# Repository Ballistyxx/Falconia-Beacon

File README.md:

# Falconia Beacon

Falconia Beacon is an ATTINY816-based, CR2032-powered LED beacon board used to make the Falconia rover visible to the SMCS Pi-in-the-sky satellite.

## What It Does

- Blinks onboard LEDs so the satellite can detect the rover location.
- Uses a potentiometer to enable or disable the blinking program.
- Supports I2C control at address `0x42`.

## Project Layout

- `PCB/`  
  Hardware design and manufacturing assets:
  - KiCad schematic and PCB files
  - 3D models and custom footprints/symbol libraries
  - Panelization and production outputs

- `src/`  
  Firmware source flashed to the board by default:
  - Main beacon firmware and related examples
  - Build files (Makefile)

## Hardware Summary

- MCU: Microchip ATTINY816
- Power: CR2032 coin cell
- Interface: I2C (address `0x42`)
- User control: Potentiometer (blink program on/off)

## Firmware

The default board firmware lives in `src/` and is intended to be the code programmed onto production boards unless otherwise noted.

Typical workflow:

1. Build firmware from the `src/` directory.
2. Flash using your ATTINY816 programming setup.
3. Validate LED blink behavior and I2C response at address `0x42`.

## Notes

- Hardware and firmware are versioned together in this repository.
- For board-level updates, start in `PCB/`.
- For behavior/protocol updates, start in `src/`.

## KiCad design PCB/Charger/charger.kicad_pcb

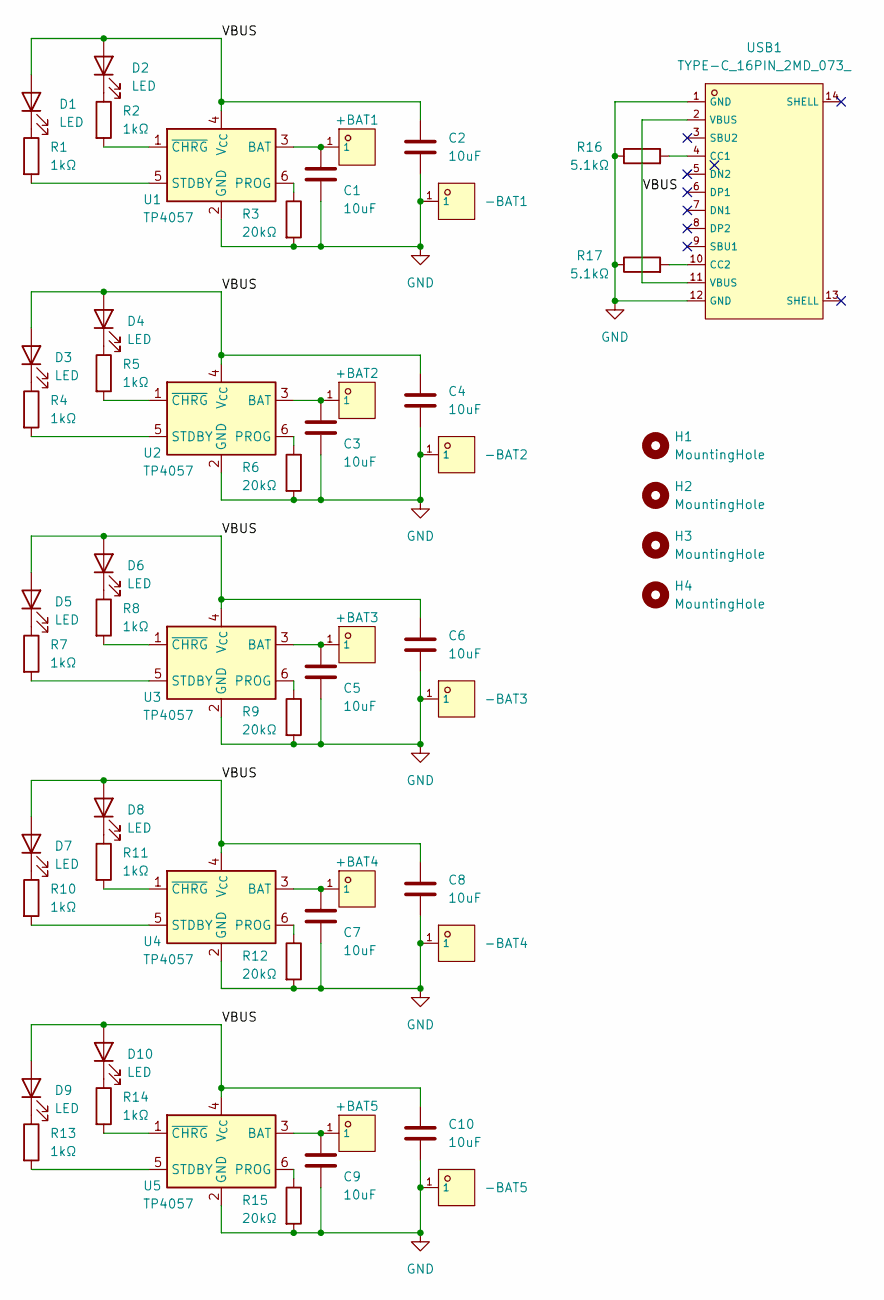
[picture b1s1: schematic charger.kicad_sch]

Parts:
+BAT1, +BAT2, +BAT3, +BAT4, +BAT5: YTC1P-6030-01; SMD-1_BD2.0-H10.0; LCSC C5221285
-BAT1, -BAT2, -BAT3, -BAT4, -BAT5: YTC1P-6030-01; SMD-1_BD2.0-H10.0; LCSC C5221285
C1, C2, C3, C4, C5, C6, C7, C8, C9, C10: 10uF; C_0603_1608Metric
D1, D2, D3, D4, D5, D6, D7, D8, D9, D10: LED; LED_0603_1608Metric
H1, H2, H3, H4: MountingHole; MountingHole_3.2mm_M3_ISO7380_Pad
R1, R2, R4, R5, R7, R8, R10, R11, R13, R14: 1kΩ; R_0603_1608Metric
R3, R6, R9, R12, R15: 20kΩ; R_0603_1608Metric
R16, R17: 5.1kΩ; R_0805_2012Metric
U1, U2, U3, U4, U5: TP4057; TSOT-23-6
USB1: TYPE-C_16PIN_2MD_073_; USB-C-SMD_TYPE-C-6PIN-2MD-073; LCSC C2765186

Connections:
/VBUS: C2.1, C4.1, C6.1, C8.1, C10.1, D1.2 (A), D2.2 (A), D3.2 (A), D4.2 (A), D5.2 (A), D6.2 (A), D7.2 (A), D8.2 (A), D9.2 (A), D10.2 (A), U1.4 (V_{CC}), U2.4 (V_{CC}), U3.4 (V_{CC}), U4.4 (V_{CC}), U5.4 (V_{CC}), USB1.2 (VBUS), USB1.11 (VBUS)
GND: -BAT1.1, -BAT2.1, -BAT3.1, -BAT4.1, -BAT5.1, C1.2, C2.2, C3.2, C4.2, C5.2, C6.2, C7.2, C8.2, C9.2, C10.2, R3.2, R6.2, R9.2, R12.2, R15.2, R16.1, R17.1, U1.2 (GND), U2.2 (GND), U3.2 (GND), U4.2 (GND), U5.2 (GND), USB1.1 (GND), USB1.12 (GND)
unnamed: D1.1 (K), R1.1
unnamed: D2.1 (K), R2.1
unnamed: D3.1 (K), R4.1
unnamed: D4.1 (K), R5.1
unnamed: D5.1 (K), R7.1
unnamed: D6.1 (K), R8.1
unnamed: D7.1 (K), R10.1
unnamed: D8.1 (K), R11.1
unnamed: D9.1 (K), R13.1
unnamed: D10.1 (K), R14.1
unnamed: +BAT1.1, C1.1, U1.3 (BAT)
unnamed: R3.1, U1.6 (PROG)
unnamed: R1.2, U1.5 (STDBY)
unnamed: R2.2, U1.1 (~CHRG)
unnamed: +BAT2.1, C3.1, U2.3 (BAT)
unnamed: R6.1, U2.6 (PROG)
unnamed: R4.2, U2.5 (STDBY)
unnamed: R5.2, U2.1 (~CHRG)
unnamed: +BAT3.1, C5.1, U3.3 (BAT)
unnamed: R9.1, U3.6 (PROG)
unnamed: R7.2, U3.5 (STDBY)
unnamed: R8.2, U3.1 (~CHRG)
unnamed: +BAT4.1, C7.1, U4.3 (BAT)
unnamed: R12.1, U4.6 (PROG)
unnamed: R10.2, U4.5 (STDBY)
unnamed: R11.2, U4.1 (~CHRG)
unnamed: +BAT5.1, C9.1, U5.3 (BAT)
unnamed: R15.1, U5.6 (PROG)
unnamed: R13.2, U5.5 (STDBY)
unnamed: R14.2, U5.1 (~CHRG)
unnamed: R16.2, USB1.4 (CC1)
unnamed: R17.2, USB1.10 (CC2)

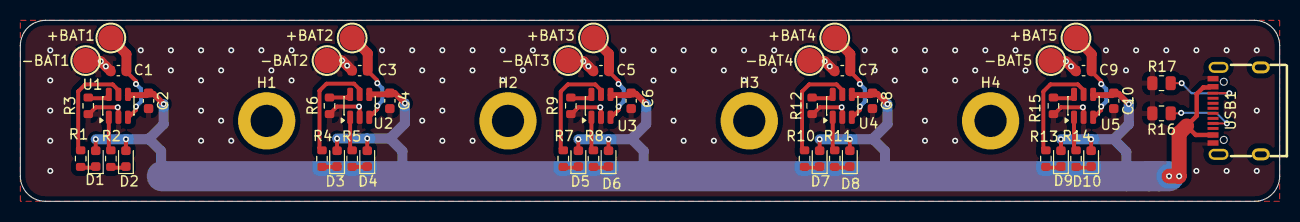
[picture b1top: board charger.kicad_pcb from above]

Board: 2 copper layers, 125.2 x 18.0 mm, 57 parts (0 on the bottom side), 34 nets.

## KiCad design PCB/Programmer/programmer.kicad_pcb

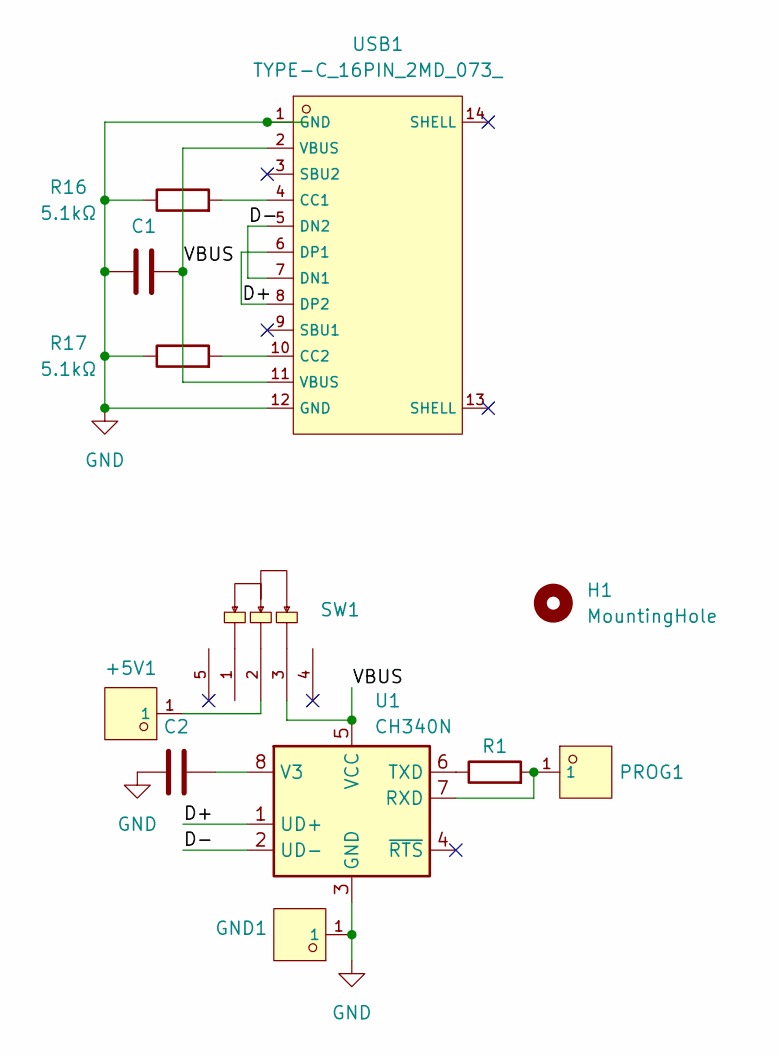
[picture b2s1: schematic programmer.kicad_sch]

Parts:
+5V1: YTC1P-6030-01; SMD-1_BD2.0-H10.0; LCSC C5221285
C1, C2: 100nF; C_0402_1005Metric
GND1: YTC1P-6030-01; SMD-1_BD2.0-H10.0; LCSC C5221285
H1: MountingHole; MountingHole_3.2mm_M3_DIN965_Pad
PROG1: YTC1P-6030-01; SMD-1_BD2.0-H10.0; LCSC C5221285
R1: 10kΩ; R_0402_1005Metric
R16, R17: 5.1kΩ; R_0805_2012Metric
SW1: SK12D07VG3_C431547; SW-TH_SK12D07VG3; LCSC C431547
U1: CH340N; JEITA_SOIC-8_3.9x4.9mm_P1.27mm
USB1: TYPE-C_16PIN_2MD_073_; USB-C-SMD_TYPE-C-6PIN-2MD-073; LCSC C2765186

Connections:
/D+: U1.1 (UD+), USB1.6 (DP1), USB1.8 (DP2)
/D-: U1.2 (UD-), USB1.5 (DN2), USB1.7 (DN1)
/VBUS: C1.2, SW1.3, U1.5 (VCC), USB1.2 (VBUS), USB1.11 (VBUS)
GND: C1.1, C2.1, GND1.1, R16.1, R17.1, U1.3 (GND), USB1.1 (GND), USB1.12 (GND)
unnamed: +5V1.1, SW1.2
unnamed: PROG1.1, R1.2, U1.7 (RXD)
unnamed: R1.1, U1.6 (TXD)
unnamed: C2.2, U1.8 (V3)
unnamed: R16.2, USB1.4 (CC1)
unnamed: R17.2, USB1.10 (CC2)

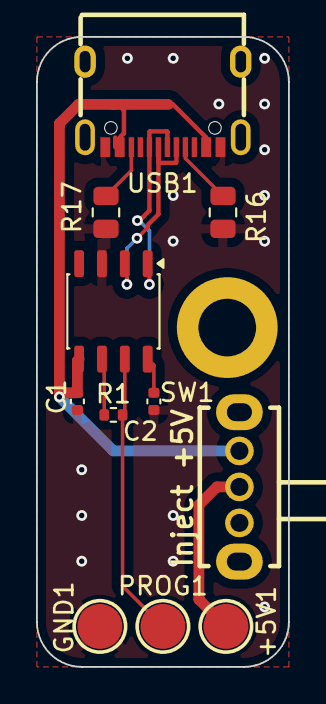
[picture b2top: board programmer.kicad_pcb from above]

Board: 2 copper layers, 14.0 x 35.0 mm, 12 parts (0 on the bottom side), 10 nets.

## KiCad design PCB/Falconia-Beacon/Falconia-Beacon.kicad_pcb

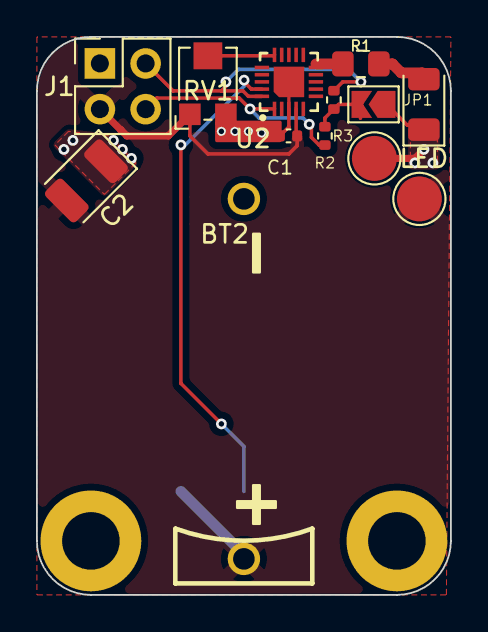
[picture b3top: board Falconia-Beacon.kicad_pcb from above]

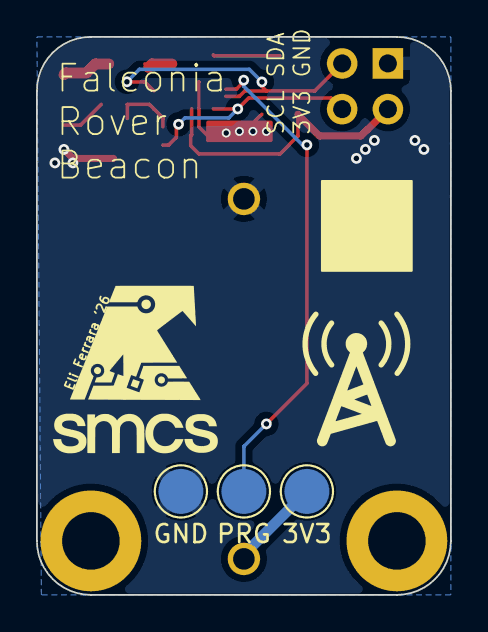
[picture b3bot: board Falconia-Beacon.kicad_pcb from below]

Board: 2 copper layers, 23.0 x 31.0 mm, 14 parts (3 on the bottom side), 9 nets.

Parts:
3V3: TestPoint_Pad_D2.5mm
BT2: BS-02-A1AJ010; BAT-TH_BS-02-A1AJ010
C1: 100nF; C_0402_1005Metric
C2: 100uF; CP_EIA-3528-21_Kemet-B
GND: TestPoint_Pad_D2.5mm
J1: Conn_02x02_Odd_Even; PinHeader_2x02_P2.54mm_Vertical
JP1: SolderJumper_2_Open; SolderJumper-2_P1.3mm_Open_TrianglePad1.0x1.5mm
LED: LED; LED_1206_3216Metric
PRG: TestPoint_Pad_D2.5mm
R1: 33Ω; R_0805_2012Metric_Pad1.20x1.40mm_HandSolder
R2, R3: 2.2kΩ; R_0402_1005Metric
RV1: R_Potentiometer; Potentiometer_Bourns_TC33X_Vertical
U2: ATTINY816-MNR; UQFN-20_L3.0-W3.0-P0.40-BL-EP1.7

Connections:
+3.3V: 3V3.1, BT2.2, C1.2, C2.2, J1.3, RV1.1, U2.4 (VDD)
/SCL: J1.4, R2.2, U2.1 (PA2)
/SDA: J1.2, R3.2, U2.20 (PA1)
/UPDI: PRG.1, U2.19 (PA0/RESET#/UPDI)
GND: BT2.1, C1.1, C2.1, GND.1, J1.1, JP1.1 (A), LED.1 (K), RV1.3, U2.3 (GND), U2.21 (GND)
unnamed: JP1.2 (B), R2.1, R3.1
unnamed: LED.2 (A), R1.1
unnamed: R1.2, U2.10 (PB4)
unnamed: RV1.2, U2.15 (PC0)

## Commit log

2026-04-19 add readme
